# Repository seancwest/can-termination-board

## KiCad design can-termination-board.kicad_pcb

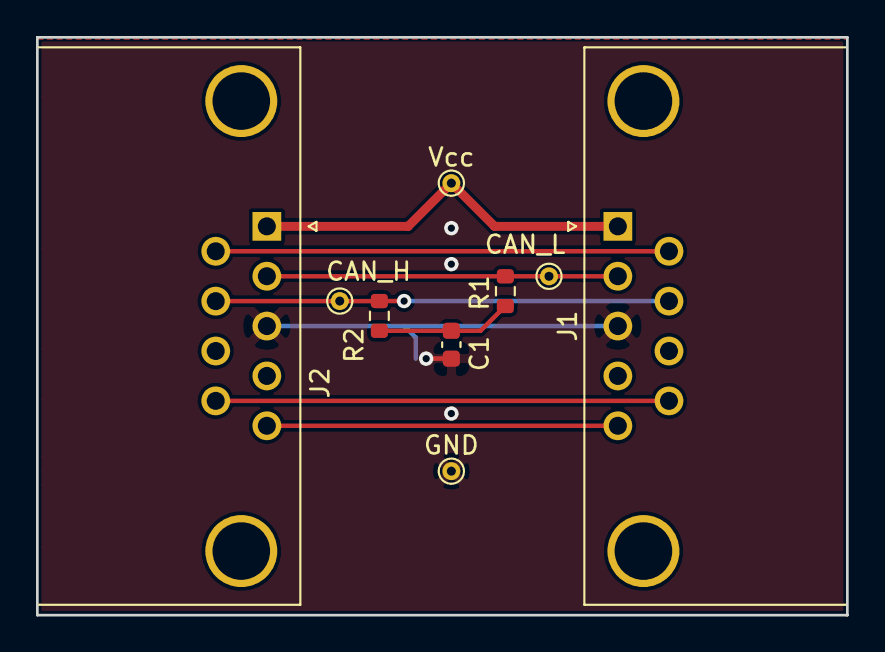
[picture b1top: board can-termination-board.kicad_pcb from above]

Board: 2 copper layers, 45.0 x 32.1 mm, 9 parts (0 on the bottom side), 8 nets.

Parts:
C1: 4.7nF; C_0603_1608Metric
CAN_H: TestPoint_THTPad_D1.0mm_Drill0.5mm
CAN_L: TestPoint_THTPad_D1.0mm_Drill0.5mm
GND: TestPoint_THTPad_D1.0mm_Drill0.5mm
J1: DB9_Female; DSUB-9_Female_Horizontal_P2.77x2.84mm_EdgePinOffset9.90mm_H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
J2: DB9_Male; DSUB-9_Male_Horizontal_P2.77x2.84mm_EdgePinOffset9.90mm_Hou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
R1, R2: 60ohm; R_0603_1608Metric
Vcc: TestPoint_THTPad_D1.0mm_Drill0.5mm

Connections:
/CAN_H: CAN_H.1, J1.7, J2.7, R2.2
/CAN_L: CAN_L.1, J1.2, J2.2, R1.2
/CAN_Shield: J1.5, J2.5
/Gnd: C1.1, GND.1, J1.3, J2.3
/Gnd_option: J1.6, J2.6
/Vcc: J1.1, J2.1, Vcc.1
/Vcc_Option: J1.9, J2.9
unnamed: C1.2, R1.1, R2.1

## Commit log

2021-03-04 Upload design files
